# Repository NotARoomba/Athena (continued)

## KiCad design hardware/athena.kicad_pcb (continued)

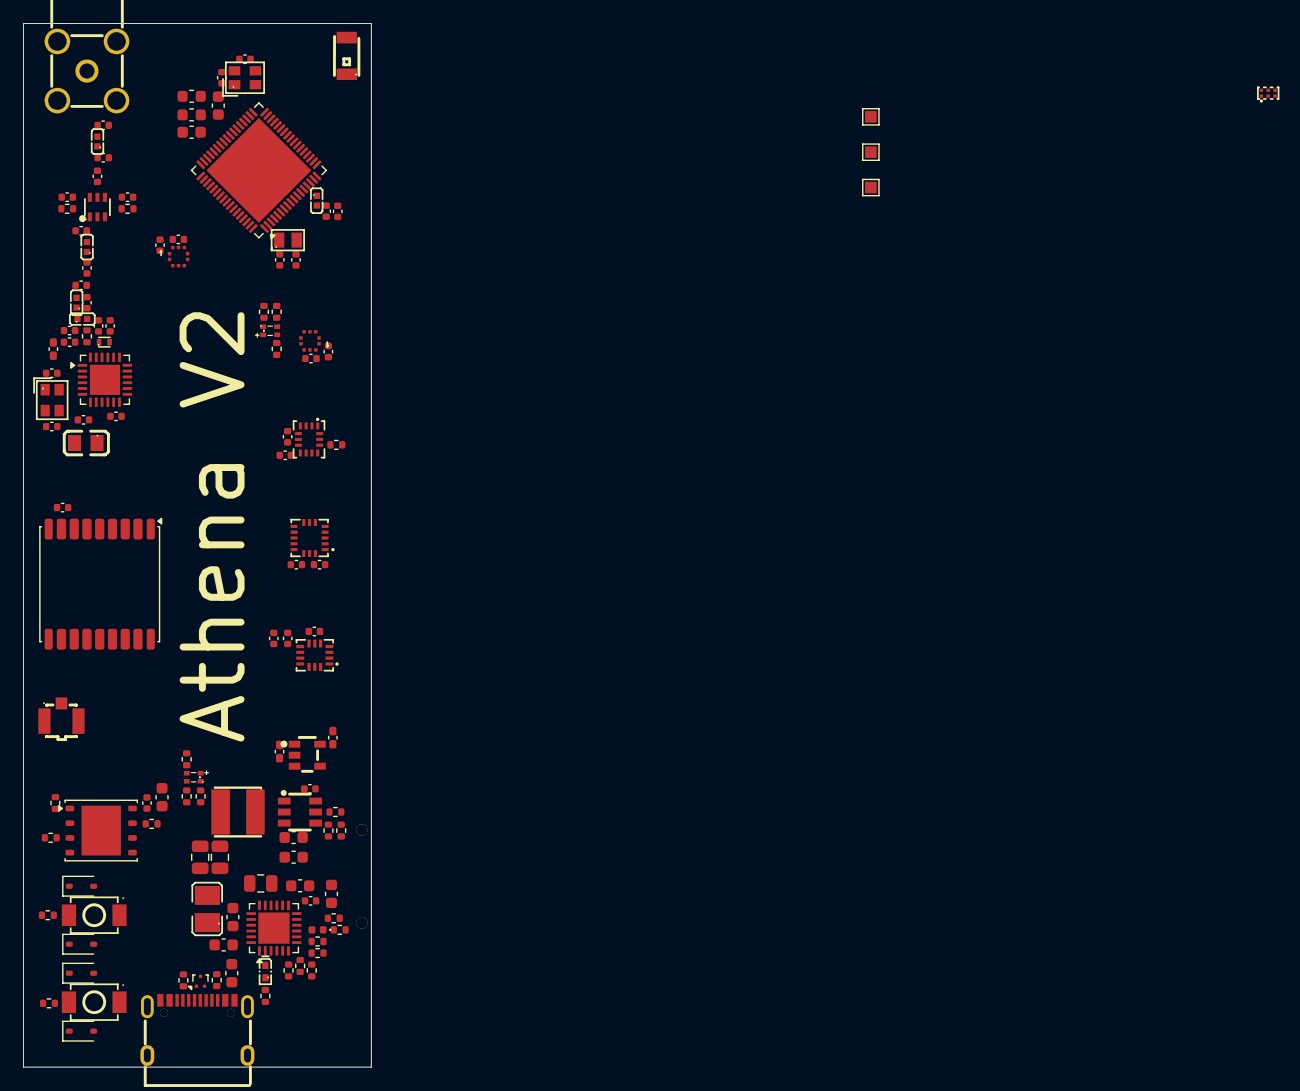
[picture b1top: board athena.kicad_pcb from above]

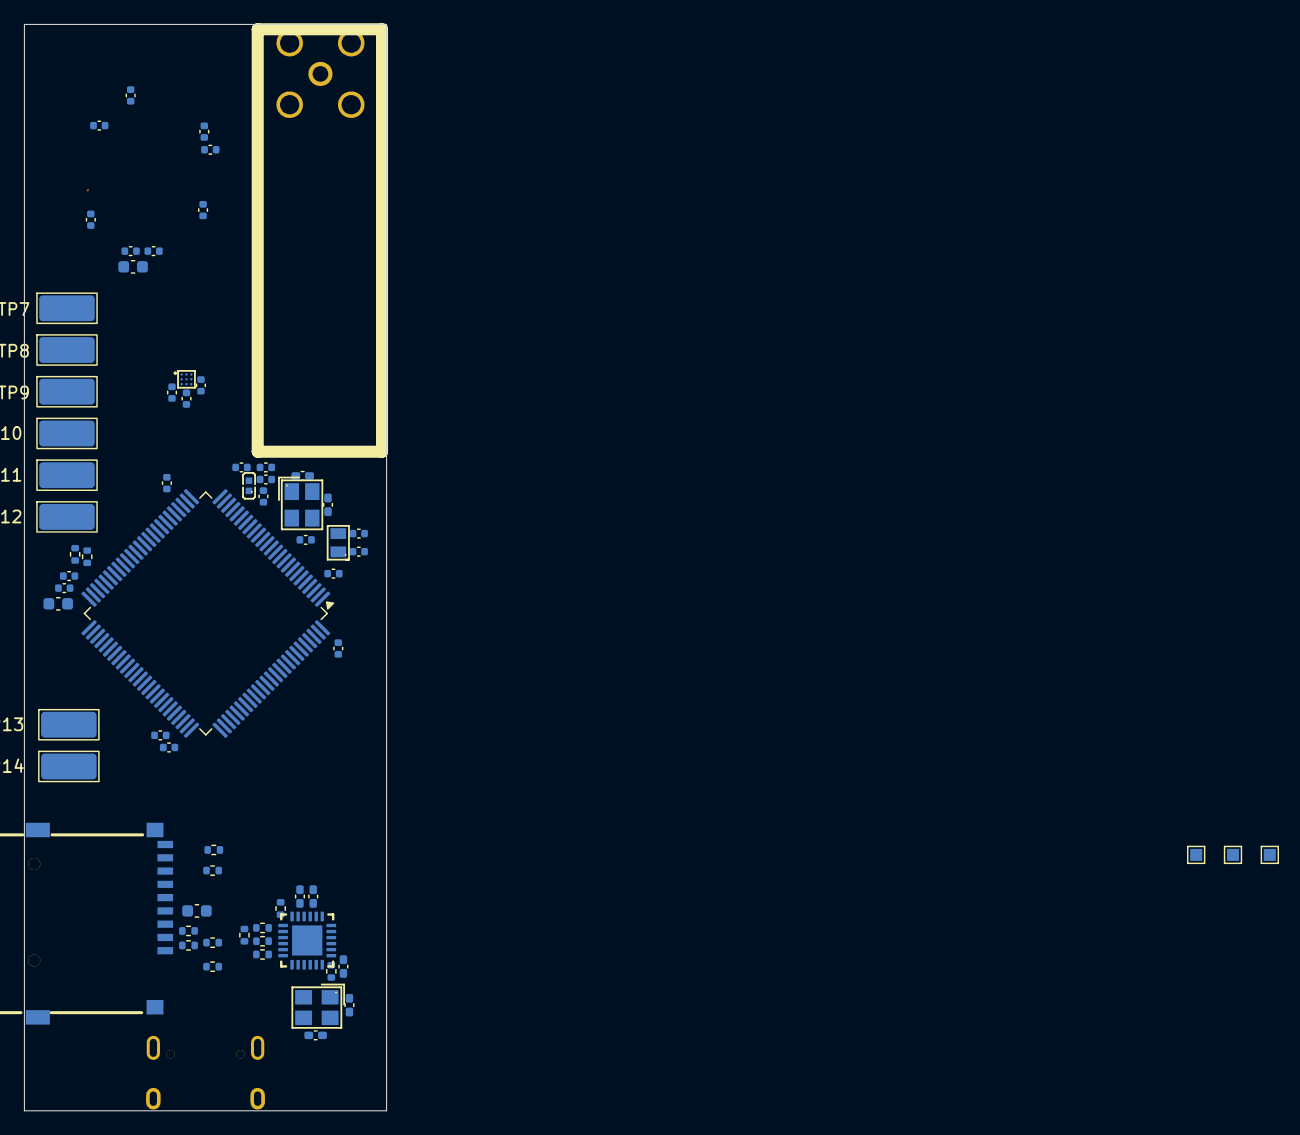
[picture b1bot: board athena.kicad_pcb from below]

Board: 4 copper layers, 30.0 x 90.0 mm, 196 parts (68 on the bottom side), 149 nets.

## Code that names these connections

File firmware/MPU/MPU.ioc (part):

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Mcu.Name=STM32F405VGTx
Mcu.Package=LQFP100
Mcu.UserName=STM32F405VGTx
PA0-WKUP.GPIOParameters=GPIO_Label
PA0-WKUP.GPIO_Label=MPU_R
PA0-WKUP.Signal=S_TIM2_CH1_ETR
PA1.GPIOParameters=GPIO_Label
PA1.GPIO_Label=MPU_G
PA1.Signal=S_TIM2_CH2
PA10.GPIOParameters=GPIO_Label
PA10.GPIO_Label=TPU_RX
PA10.Mode=Multiprocessor_communication
PA10.Signal=USART1_RX
PA11.Mode=Device_Only
PA11.Signal=USB_OTG_FS_DM
PA12.Mode=Device_Only
PA12.Signal=USB_OTG_FS_DP
PA13.Mode=Serial_Wire
PA13.Signal=SYS_JTMS-SWDIO
PA14.Mode=Serial_Wire
PA14.Signal=SYS_JTCK-SWCLK
PA2.GPIOParameters=GPIO_Label
PA2.GPIO_Label=MPU_B
PA2.Signal=S_TIM2_CH3
PA5.GPIOParameters=GPIO_Label
PA5.GPIO_Label=IMU_SCK
PA5.Mode=Full_Duplex_Master
PA5.Signal=SPI1_SCK
PA6.GPIOParameters=GPIO_Label
PA6.GPIO_Label=IMU_MISO
PA6.Mode=Full_Duplex_Master
PA6.Signal=SPI1_MISO
PA7.GPIOParameters=GPIO_Label
PA7.GPIO_Label=IMU_MOSI
PA7.Mode=Full_Duplex_Master
PA7.Signal=SPI1_MOSI
PA9.GPIOParameters=GPIO_Label
PA9.GPIO_Label=TPU_TX
PA9.Mode=Multiprocessor_communication
PA9.Signal=USART1_TX
PB1.GPIOParameters=GPIO_Label
PB1.GPIO_Label=MOTOR_7
PB1.Mode=PWM Generation3 CH3N
PB1.Signal=TIM8_CH3N
PB10.GPIOParameters=GPIO_Label
PB10.GPIO_Label=MAG_SCL
PB10.Mode=I2C
PB10.Signal=I2C2_SCL
PB11.GPIOParameters=GPIO_Label
PB11.GPIO_Label=MAG_SDA
PB11.Mode=I2C
PB11.Signal=I2C2_SDA
PB13.GPIOParameters=GPIO_Label
PB13.GPIO_Label=SENSOR_SCK
PB13.Mode=Full_Duplex_Master
PB13.Signal=SPI2_SCK
PB14.GPIOParameters=GPIO_Label
PB14.GPIO_Label=SENSOR_MISO
PB14.Mode=Full_Duplex_Master
PB14.Signal=SPI2_MISO
PB15.GPIOParameters=GPIO_Label
PB15.GPIO_Label=SENSOR_MOSI
PB15.Mode=Full_Duplex_Master
PB15.Signal=SPI2_MOSI
PB2.GPIOParameters=GPIO_Label
PB2.GPIO_Label=IMU_CS
PB2.Signal=GPIO_Output
PB3.GPIOParameters=GPIO_Label
PB3.GPIO_Label=FLASH_SCK
PB3.Mode=Full_Duplex_Master
PB3.Signal=SPI3_SCK
PB4.GPIOParameters=GPIO_Label
PB4.GPIO_Label=FLASH_MISO
PB4.Mode=Full_Duplex_Master
PB4.Signal=SPI3_MISO
PB5.GPIOParameters=GPIO_Label
PB5.GPIO_Label=FLASH_MOSI
PB5.Mode=Full_Duplex_Master
PB5.Signal=SPI3_MOSI
PB6.GPIOParameters=GPIO_Label
PB6.GPIO_Label=FLASH_CS
PB6.Signal=GPIO_Output
PC12.Mode=SD_1_bit
PC12.Signal=SDIO_CK
PC14-OSC32_IN.Mode=LSE-External-Oscillator
PC14-OSC32_IN.Signal=RCC_OSC32_IN
PC15-OSC32_OUT.Mode=LSE-External-Oscillator
PC15-OSC32_OUT.Signal=RCC_OSC32_OUT
PC4.GPIOParameters=GPIO_Label
PC4.GPIO_Label=BMI_INT1
PC4.Signal=GPXTI4
PC5.GPIOParameters=GPIO_Label
PC5.GPIO_Label=BMI_INT2
PC5.Signal=GPXTI5
PC6.GPIOParameters=GPIO_Label
PC6.GPIO_Label=MOTOR_5
PC6.Signal=S_TIM8_CH1
PC7.GPIOParameters=GPIO_Label
PC7.GPIO_Label=MOTOR_6
PC7.Signal=S_TIM8_CH2
PC8.Mode=SD_1_bit
PC8.Signal=SDIO_D0
PC9.GPIOParameters=GPIO_Label
PC9.GPIO_Label=MOTOR_8
PC9.Signal=S_TIM8_CH4
PD1.GPIOParameters=GPIO_Label
PD1.GPIO_Label=SD_CD
PD1.Signal=GPIO_Input
PD10.GPIOParameters=GPIO_Label
PD10.GPIO_Label=HLI_CS
PD10.Signal=GPIO_Output
PD11.GPIOParameters=GPIO_Label
PD11.GPIO_Label=HLI_INT1
PD11.Signal=GPXTI11
PD12.GPIOParameters=GPIO_Label
PD12.GPIO_Label=HLI_INT2
PD12.Signal=GPXTI12
PD2.Mode=SD_1_bit
PD2.Signal=SDIO_CMD
PD3.GPIOParameters=GPIO_Label
PD3.GPIO_Label=GPS_EXTINT
PD3.Signal=EVENTOUT
PD4.GPIOParameters=GPIO_Label
PD4.GPIO_Label=GPS_SAFEBOOT
PD4.Signal=GPIO_Output
PD5.GPIOParameters=GPIO_Label
PD5.GPIO_Label=GPS_TX
PD5.Mode=Asynchronous
PD5.Signal=USART2_TX
PD6.GPIOParameters=GPIO_Label
PD6.GPIO_Label=GPS_RX
PD6.Mode=Asynchronous
PD6.Signal=USART2_RX
PD7.GPIOParameters=GPIO_Label
PD7.GPIO_Label=GPS_RESET
PD7.Signal=GPIO_Output
PD8.GPIOParameters=GPIO_Label
PD8.GPIO_Label=BMP_CS
PD8.Signal=GPIO_Output
PD9.GPIOParameters=GPIO_Label
PD9.GPIO_Label=BMP_INT
PD9.Signal=GPXTI9
PE11.GPIOParameters=GPIO_Label
PE11.GPIO_Label=MOTOR_2
PE11.Signal=S_TIM1_CH2
PE13.GPIOParameters=GPIO_Label
PE13.GPIO_Label=MOTOR_3
PE13.Signal=S_TIM1_CH3
PE14.GPIOParameters=GPIO_Label
PE14.GPIO_Label=MOTOR_4
PE14.Signal=S_TIM1_CH4
PE15.GPIOParameters=GPIO_Label
PE15.GPIO_Label=MAG_INT
PE15.Signal=GPXTI15
PE7.GPIOParameters=GPIO_Label
PE7.GPIO_Label=IMU_INT1
PE7.Signal=GPXTI7
PE8.GPIOParameters=GPIO_Label
PE8.GPIO_Label=IMU_INT2
PE8.Signal=GPXTI8
PE9.GPIOParameters=GPIO_Label
PE9.GPIO_Label=MOTOR_1
PE9.Signal=S_TIM1_CH1
PH0-OSC_IN.Mode=HSE-External-Oscillator
PH0-OSC_IN.Signal=RCC_OSC_IN
PH1-OSC_OUT.Mode=HSE-External-Oscillator
PH1-OSC_OUT.Signal=RCC_OSC_OUT
RCC.HSE_VALUE=25000000
RCC.SYSCLKFreq_VALUE=16000000
board=custom

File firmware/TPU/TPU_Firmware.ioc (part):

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Mcu.Name=STM32H743VITx
Mcu.Package=LQFP100
Mcu.UserName=STM32H743VITx
PA0.GPIOParameters=PinState,GPIO_Label
PA0.GPIO_Label=RF_RESET
PA0.PinState=GPIO_PIN_SET
PA0.Signal=GPIO_Output
PA1.GPIOParameters=GPIO_Label
PA1.GPIO_Label=FLASH_IO3
PA1.Mode=Single Bank 1
PA1.Signal=QUADSPI_BK1_IO3
PA10.GPIOParameters=GPIO_Label
PA10.GPIO_Label=TPU_RX_EX
PA10.Mode=Asynchronous
PA10.Signal=USART1_RX
PA11.Mode=Device_Only
PA11.Signal=USB_OTG_FS_DM
PA12.Mode=Device_Only
PA12.Signal=USB_OTG_FS_DP
PA15\ (JTDI).GPIOParameters=GPIO_Label
PA15\ (JTDI).GPIO_Label=GPS_TIMEPULSE
PA15\ (JTDI).Signal=S_TIM2_CH1_ETR
PA2.GPIOParameters=GPIO_Label
PA2.GPIO_Label=RF_DIO4
PA2.Signal=GPIO_Input
PA3.GPIOParameters=GPIO_Label
PA3.GPIO_Label=RF_DIO5
PA3.Signal=GPIO_Input
PA4.GPIOParameters=PinState,GPIO_Label
PA4.GPIO_Label=RF_CS
PA4.PinState=GPIO_PIN_SET
PA4.Signal=GPIO_Output
PA5.GPIOParameters=GPIO_Label
PA5.GPIO_Label=RF_SCK
PA5.Mode=Full_Duplex_Master
PA5.Signal=SPI1_SCK
PA6.GPIOParameters=GPIO_Label
PA6.GPIO_Label=RF_MISO
PA6.Mode=Full_Duplex_Master
PA6.Signal=SPI1_MISO
PA7.GPIOParameters=GPIO_Label
PA7.GPIO_Label=RF_MOSI
PA7.Mode=Full_Duplex_Master
PA7.Signal=SPI1_MOSI
PA9.GPIOParameters=GPIO_Label
PA9.GPIO_Label=TPU_TX_EX
PA9.Mode=Asynchronous
PA9.Signal=USART1_TX
PB0.GPIOParameters=GPIO_Label
PB0.GPIO_Label=RF_DIO1
PB0.Signal=GPIO_Input
PB1.GPIOParameters=GPIO_Label
PB1.GPIO_Label=RF_DIO0
PB1.Signal=GPIO_Input
PB10.GPIOParameters=GPIO_Label
PB10.GPIO_Label=FLASH_CS
PB10.Mode=Single Bank 1
PB10.Signal=QUADSPI_BK1_NCS
PB12.GPIOParameters=GPIO_Label
PB12.GPIO_Label=TPU_CAN_RX
PB12.Mode=FDCAN_Activate
PB12.Signal=FDCAN2_RX
PB13.GPIOParameters=GPIO_Label
PB13.GPIO_Label=TPU_CAN_TX
PB13.Mode=FDCAN_Activate
PB13.Signal=FDCAN2_TX
PB14.GPIOParameters=GPIO_Label
PB14.GPIO_Label=TPU_CAN_S
PB14.Signal=GPIO_Output
PB15.GPIOParameters=PinState,GPIO_Label
PB15.GPIO_Label=TPU_R
PB15.PinState=GPIO_PIN_SET
PB15.Signal=GPIO_Output
PB2.GPIOParameters=GPIO_Label
PB2.GPIO_Label=FLASH_SCK
PB2.Mode=Single Bank 1
PB2.Signal=QUADSPI_CLK
PB3\ (JTDO/TRACESWO).GPIOParameters=GPIO_Label
PB3\ (JTDO/TRACESWO).GPIO_Label=GPS_SCK
PB3\ (JTDO/TRACESWO).Mode=Full_Duplex_Master
PB3\ (JTDO/TRACESWO).Signal=SPI3_SCK
PB4\ (NJTRST).GPIOParameters=GPIO_Label
PB4\ (NJTRST).GPIO_Label=GPS_MISO
PB4\ (NJTRST).Mode=Full_Duplex_Master
PB4\ (NJTRST).Signal=SPI3_MISO
PB5.GPIOParameters=GPIO_Label
PB5.GPIO_Label=GPS_EXTINT
PB5.Signal=GPXTI5
PB6.GPIOParameters=PinState,GPIO_Label
PB6.GPIO_Label=GPS_RESET
PB6.PinState=GPIO_PIN_SET
PB6.Signal=GPIO_Output
PC10.GPIOParameters=GPIO_Label
PC10.GPIO_Label=SD_DAT2
PC10.Mode=SD_4_bits_Wide_bus
PC10.Signal=SDMMC1_D2
PC11.GPIOParameters=GPIO_Label
PC11.GPIO_Label=SD_DAT3
PC11.Mode=SD_4_bits_Wide_bus
PC11.Signal=SDMMC1_D3
PC12.GPIOParameters=GPIO_Label
PC12.GPIO_Label=SD_SCK
PC12.Mode=SD_4_bits_Wide_bus
PC12.Signal=SDMMC1_CK
PC14-OSC32_IN\ (OSC32_IN).Mode=LSE-External-Oscillator
PC14-OSC32_IN\ (OSC32_IN).Signal=RCC_OSC32_IN
PC15-OSC32_OUT\ (OSC32_OUT).Mode=LSE-External-Oscillator
PC15-OSC32_OUT\ (OSC32_OUT).Signal=RCC_OSC32_OUT
PC4.GPIOParameters=GPIO_Label
PC4.GPIO_Label=RF_DIO3
PC4.Signal=GPIO_Input
PC5.GPIOParameters=GPIO_Label
PC5.GPIO_Label=RF_DIO2
PC5.Signal=GPIO_Input
PC8.GPIOParameters=GPIO_Label
PC8.GPIO_Label=SD_DAT0
PC8.Mode=SD_4_bits_Wide_bus
PC8.Signal=SDMMC1_D0
PC9.GPIOParameters=GPIO_Label
PC9.GPIO_Label=SD_DAT1
PC9.Mode=SD_4_bits_Wide_bus
PC9.Signal=SDMMC1_D1
PD1.GPIOParameters=GPIO_Label
PD1.GPIO_Label=SD_CD
PD1.Signal=GPIO_Input
PD11.GPIOParameters=GPIO_Label
PD11.GPIO_Label=FLASH_IO0
PD11.Mode=Single Bank 1
PD11.Signal=QUADSPI_BK1_IO0
PD12.GPIOParameters=GPIO_Label
PD12.GPIO_Label=FLASH_IO1
PD12.Mode=Single Bank 1
PD12.Signal=QUADSPI_BK1_IO1
PD2.GPIOParameters=GPIO_Label
PD2.GPIO_Label=SD_CMD
PD2.Mode=SD_4_bits_Wide_bus
PD2.Signal=SDMMC1_CMD
PD3.GPIOParameters=GPIO_Label
PD3.GPIO_Label=GPS_SEL
PD3.Signal=GPIO_Output
PD4.GPIOParameters=PinState,GPIO_Label
PD4.GPIO_Label=GPS_SAFEBOOT
PD4.PinState=GPIO_PIN_SET
PD4.Signal=GPIO_Output
PD5.GPIOParameters=GPIO_Label
PD5.GPIO_Label=GPS_LNA_EN
PD5.Signal=GPIO_Input
PD6.GPIOParameters=GPIO_Label
PD6.GPIO_Label=GPS_MOSI
PD6.Mode=Full_Duplex_Master
PD6.Signal=SPI3_MOSI
PD7.GPIOParameters=PinState,GPIO_Label
PD7.GPIO_Label=GPS_CS
PD7.PinState=GPIO_PIN_SET
PD7.Signal=GPIO_Output
PD8.GPIOParameters=PinState,GPIO_PuPd,GPIO_Label,GPIO_ModeDefaultOutputPP
PD8.GPIO_Label=TPU_G
PD8.GPIO_ModeDefaultOutputPP=GPIO_MODE_OUTPUT_PP
PD8.GPIO_PuPd=GPIO_NOPULL
PD8.PinState=GPIO_PIN_SET
PD8.Signal=GPIO_Output
PD9.GPIOParameters=PinState,GPIO_PuPd,GPIO_Label
PD9.GPIO_Label=TPU_B
PD9.GPIO_PuPd=GPIO_NOPULL
PD9.PinState=GPIO_PIN_SET
PD9.Signal=GPIO_Output
PE0.GPIOParameters=GPIO_Label
PE0.GPIO_Label=TPU_TX
PE0.Mode=Asynchronous
PE0.Signal=UART8_RX
PE1.GPIOParameters=GPIO_Label
PE1.GPIO_Label=TPU_RX
PE1.Mode=Asynchronous
PE1.Signal=UART8_TX
PE12.GPIOParameters=GPIO_Label
PE12.GPIO_Label=MCU_SCK
PE12.Mode=Full_Duplex_Slave
PE12.Signal=SPI4_SCK
PE13.GPIOParameters=GPIO_Label
PE13.GPIO_Label=TPU_SELECT
PE13.Signal=GPIO_Input
PE2.GPIOParameters=GPIO_Label
PE2.GPIO_Label=FLASH_IO2
PE2.Mode=Single Bank 1
PE2.Signal=QUADSPI_BK1_IO2
PE5.GPIOParameters=GPIO_Label
PE5.GPIO_Label=MCU_MISO
PE5.Mode=Full_Duplex_Slave
PE5.Signal=SPI4_MISO
PE6.GPIOParameters=GPIO_Label
PE6.GPIO_Label=MCU_MOSI
PE6.Mode=Full_Duplex_Slave
PE6.Signal=SPI4_MOSI
PE7.GPIOParameters=GPIO_Label
PE7.GPIO_Label=BT_RX
PE7.Mode=Asynchronous
PE7.Signal=UART7_RX
PE8.GPIOParameters=GPIO_Label
PE8.GPIO_Label=BT_TX
PE8.Mode=Asynchronous
PE8.Signal=UART7_TX
PE9.GPIOParameters=GPIO_Label
PE9.GPIO_Label=BT_RESET
PE9.Signal=GPIO_Input
PH0-OSC_IN\ (PH0).Mode=HSE-External-Oscillator
PH0-OSC_IN\ (PH0).Signal=RCC_OSC_IN
PH1-OSC_OUT\ (PH1).Mode=HSE-External-Oscillator
PH1-OSC_OUT\ (PH1).Signal=RCC_OSC_OUT
RCC.SYSCLKFreq_VALUE=75000000
RCC.SYSCLKSource=RCC_SYSCLKSOURCE_PLLCLK
board=custom

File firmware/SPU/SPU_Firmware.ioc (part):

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Mcu.Name=STM32G474R(B-C-E)Tx
Mcu.Package=LQFP64
Mcu.UserName=STM32G474RETx
PA0.GPIOParameters=GPIO_Label
PA0.GPIO_Label=SERVO5_PWM
PA0.Signal=S_TIM2_CH1
PA1.GPIOParameters=GPIO_Label
PA1.GPIO_Label=SERVO6_PWM
PA1.Signal=S_TIM2_CH2
PA10.GPIOParameters=GPIO_Label
PA10.GPIO_Label=PYRO_1
PA10.Signal=GPIO_Output
PA11.Mode=Device
PA11.Signal=USB_DM
PA12.Mode=Device
PA12.Signal=USB_DP
PA13.GPIOParameters=GPIO_PuPd,GPIO_Label
PA13.GPIO_Label=SPU_PD_SCL
PA13.GPIO_PuPd=GPIO_PULLUP
PA13.Mode=I2C
PA13.Signal=I2C1_SCL
PA14.GPIOParameters=GPIO_PuPd,GPIO_Label
PA14.GPIO_Label=SPU_PD_SDA
PA14.GPIO_PuPd=GPIO_PULLUP
PA14.Mode=I2C
PA14.Signal=I2C1_SDA
PA15.GPIOParameters=GPIO_Label
PA15.GPIO_Label=SPU_PD_IRQ
PA15.Signal=GPXTI15
PA3.GPIOParameters=GPIO_PuPd,GPIO_Label
PA3.GPIO_Label=PD_IRQ
PA3.GPIO_PuPd=GPIO_PULLUP
PA3.Signal=GPIO_Input
PA4.GPIOParameters=GPIO_Label
PA4.GPIO_Label=SPU_SELECT
PA4.Signal=GPIO_Output
PA5.GPIOParameters=GPIO_Label
PA5.GPIO_Label=MCU_SCK
PA5.Mode=Full_Duplex_Slave
PA5.Signal=SPI1_SCK
PA6.GPIOParameters=GPIO_Label
PA6.GPIO_Label=MCU_MISO
PA6.Mode=Full_Duplex_Slave
PA6.Signal=SPI1_MISO
PA7.GPIOParameters=GPIO_Label
PA7.GPIO_Label=MCU_MOSI
PA7.Mode=Full_Duplex_Slave
PA7.Signal=SPI1_MOSI
PA8.GPIOParameters=GPIO_Label
PA8.GPIO_Label=PYRO_3
PA8.Signal=GPIO_Output
PA9.GPIOParameters=GPIO_Label
PA9.GPIO_Label=PYRO_2
PA9.Signal=GPIO_Output
PB0.GPIOParameters=GPIO_Label
PB0.GPIO_Label=SERVO1_EN
PB0.Signal=GPIO_Output
PB1.GPIOParameters=GPIO_Label
PB1.GPIO_Label=SERVO2_EN
PB1.Signal=GPIO_Output
PB11.GPIOParameters=PinState,GPIO_Label
PB11.GPIO_Label=SPU_B
PB11.PinState=GPIO_PIN_SET
PB11.Signal=GPIO_Output
PB12.GPIOParameters=PinState,GPIO_Label
PB12.GPIO_Label=SPU_G
PB12.PinState=GPIO_PIN_SET
PB12.Signal=GPIO_Output
PB13.GPIOParameters=PinState,GPIO_Label
PB13.GPIO_Label=SPU_R
PB13.PinState=GPIO_PIN_SET
PB13.Signal=GPIO_Output
PB14.GPIOParameters=GPIO_Label
PB14.GPIO_Label=SERVO4_EN
PB14.Signal=GPIO_Output
PB15.GPIOParameters=GPIO_Label
PB15.GPIO_Label=SERVO5_EN
PB15.Signal=GPIO_Output
PB2.GPIOParameters=GPIO_Label
PB2.GPIO_Label=SERVO3_EN
PB2.Signal=GPIO_Output
PB3.GPIOParameters=GPIO_Label
PB3.GPIO_Label=EN_OTG
PB3.Signal=GPIO_Output
PB4.GPIOParameters=GPIO_Label
PB4.GPIO_Label=CHRG_OK
PB4.Signal=GPIO_Input
PB5.GPIOParameters=GPIO_Label
PB5.GPIO_Label=SPU_CAN_RX
PB5.Mode=FDCAN_Activate
PB5.Signal=FDCAN2_RX
PB6.GPIOParameters=GPIO_Label
PB6.GPIO_Label=SPU_CAN_TX
PB6.Mode=FDCAN_Activate
PB6.Signal=FDCAN2_TX
PB7.GPIOParameters=PinState,GPIO_Label
PB7.GPIO_Label=SPU_CAN_S
PB7.PinState=GPIO_PIN_SET
PB7.Signal=GPIO_Output
PB9.GPIOParameters=PinState,GPIO_Label
PB9.GPIO_Label=RESET_MPU
PB9.PinState=GPIO_PIN_SET
PB9.Signal=GPIO_Output
PC0.GPIOParameters=GPIO_Label
PC0.GPIO_Label=SERVO1_PWM
PC0.Signal=S_TIM1_CH1
PC1.GPIOParameters=GPIO_Label
PC1.GPIO_Label=SERVO2_PWM
PC1.Signal=S_TIM1_CH2
PC10.GPIOParameters=GPIO_Label
PC10.GPIO_Label=SPU_PROCHOT
PC10.Signal=GPIO_Input
PC11.GPIOParameters=GPIO_Label
PC11.GPIO_Label=CMPOUT
PC11.Signal=GPIO_Input
PC12.GPIOParameters=GPIO_Label
PC12.GPIO_Label=SPU_RX
PC12.Mode=Asynchronous
PC12.Signal=UART5_TX
PC14-OSC32_IN.Mode=LSE-External-Oscillator
PC14-OSC32_IN.Signal=RCC_OSC32_IN
PC15-OSC32_OUT.Mode=LSE-External-Oscillator
PC15-OSC32_OUT.Signal=RCC_OSC32_OUT
PC2.GPIOParameters=GPIO_Label
PC2.GPIO_Label=SERVO3_PWM
PC2.Signal=S_TIM1_CH3
PC3.GPIOParameters=GPIO_Label
PC3.GPIO_Label=SERVO4_PWM
PC3.Signal=S_TIM1_CH4
PC4.GPIOParameters=GPIO_Label
PC4.GPIO_Label=SPU_TX_EX
PC4.Mode=Asynchronous
PC4.Signal=USART1_TX
PC5.GPIOParameters=GPIO_Label
PC5.GPIO_Label=SPU_RX_EX
PC5.Mode=Asynchronous
PC5.Signal=USART1_RX
PC6.GPIOParameters=GPIO_Label
PC6.GPIO_Label=SERVO6_EN
PC6.Signal=GPIO_Output
PC7.GPIOParameters=GPIO_Label
PC7.GPIO_Label=PYRO_6
PC7.Signal=GPIO_Output
PC8.GPIOParameters=GPIO_Label
PC8.GPIO_Label=PYRO_5
PC8.Signal=GPIO_Output
PC9.GPIOParameters=GPIO_Label
PC9.GPIO_Label=PYRO_4
PC9.Signal=GPIO_Output
PD2.GPIOParameters=GPIO_Label
PD2.GPIO_Label=SPU_TX
PD2.Mode=Asynchronous
PD2.Signal=UART5_RX
PF0-OSC_IN.Mode=HSE-External-Oscillator
PF0-OSC_IN.Signal=RCC_OSC_IN
PF1-OSC_OUT.Mode=HSE-External-Oscillator
PF1-OSC_OUT.Signal=RCC_OSC_OUT
RCC.HSE_VALUE=24000000
RCC.SYSCLKFreq_VALUE=144000000
RCC.SYSCLKSource=RCC_SYSCLKSOURCE_PLLCLK
board=custom

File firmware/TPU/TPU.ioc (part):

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Mcu.Name=STM32WB55RGVx
Mcu.Package=VFQFPN68
Mcu.UserName=STM32WB55RGVx
PA0.GPIOParameters=GPIO_Label
PA0.GPIO_Label=TPU_R
PA0.Signal=S_TIM2_CH1
PA1.GPIOParameters=GPIO_Label
PA1.GPIO_Label=TPU_G
PA1.Signal=S_TIM2_CH2
PA11.Mode=Device
PA11.Signal=USB_DM
PA12.Mode=Device
PA12.Signal=USB_DP
PA13.Mode=Serial_Wire
PA13.Signal=SYS_JTMS-SWDIO
PA14.Mode=Serial_Wire
PA14.Signal=SYS_JTCK-SWCLK
PA2.GPIOParameters=GPIO_Label
PA2.GPIO_Label=TPU_B
PA2.Signal=S_TIM2_CH3
PA4.GPIOParameters=GPIO_Label
PA4.GPIO_Label=LORA_CS
PA4.Mode=NSS_Signal_Hard_Output
PA4.Signal=SPI1_NSS
PA5.GPIOParameters=GPIO_Label
PA5.GPIO_Label=LORA_SCK
PA5.Mode=Full_Duplex_Master
PA5.Signal=SPI1_SCK
PA6.GPIOParameters=GPIO_Label
PA6.GPIO_Label=LORA_MISO
PA6.Mode=Full_Duplex_Master
PA6.Signal=SPI1_MISO
PA7.GPIOParameters=GPIO_Label
PA7.GPIO_Label=LORA_MOSI
PA7.Mode=Full_Duplex_Master
PA7.Signal=SPI1_MOSI
PA8.GPIOParameters=GPIO_Label
PA8.GPIO_Label=LORA_BUSY
PA8.Signal=GPIO_Input
PA9.GPIOParameters=GPIO_Label
PA9.GPIO_Label=LORA_RESET
PA9.Signal=GPIO_Output
PB12.GPIOParameters=GPIO_Label
PB12.GPIO_Label=BARO_CS
PB12.Mode=NSS_Signal_Hard_Output
PB12.Signal=SPI2_NSS
PB13.GPIOParameters=GPIO_Label
PB13.GPIO_Label=BARO_SCK
PB13.Mode=Full_Duplex_Master
PB13.Signal=SPI2_SCK
PB14.GPIOParameters=GPIO_Label
PB14.GPIO_Label=BARO_MISO
PB14.Mode=Full_Duplex_Master
PB14.Signal=SPI2_MISO
PB15.GPIOParameters=GPIO_Label
PB15.GPIO_Label=BARO_MOSI
PB15.Mode=Full_Duplex_Master
PB15.Signal=SPI2_MOSI
PB6.GPIOParameters=GPIO_Label
PB6.GPIO_Label=TPU_TX
PB6.Mode=Multiprocessor_communication
PB6.Signal=USART1_TX
PB7.GPIOParameters=GPIO_Label
PB7.GPIO_Label=TPU_RX
PB7.Mode=Multiprocessor_communication
PB7.Signal=USART1_RX
PC14-OSC32_IN.Mode=LSE-External-Oscillator
PC14-OSC32_IN.Signal=RCC_OSC32_IN
PC15-OSC32_OUT.Mode=LSE-External-Oscillator
PC15-OSC32_OUT.Signal=RCC_OSC32_OUT
PC4.GPIOParameters=GPIO_Label
PC4.GPIO_Label=LORA_DIO1
PC4.Signal=GPXTI4
PC6.GPIOParameters=GPIO_Label
PC6.GPIO_Label=BARO_INT
PC6.Signal=GPXTI6
RCC.HSE_VALUE=32000000
RCC.SYSCLKFreq_VALUE=64000000
RCC.SYSCLKSource=RCC_SYSCLKSOURCE_PLLCLK
board=custom

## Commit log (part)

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2025-09-05 firmware and journal and readme
2025-09-05 added files
2025-09-05 addedheader with hours
2025-09-20 Revise power management voltage range in README
2025-10-28 psoter and stuff
2025-11-02 firmware start
2025-11-07 firmware
2025-11-11 physcial pcb
2025-11-13 flashign lights
2025-11-14 trying to get fifo
2025-12-02 no build
2025-12-02 gitignore
2025-12-03 bmp388 fifo
2025-12-03 both
2025-12-03 start imu
2025-12-03 imu stuff
2025-12-03 imu working
2026-03-09 start of v2
2026-05-19 aaaaa
2026-06-21 half of schematic
